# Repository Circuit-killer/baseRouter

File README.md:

BaseRouter
==========
Custom Router
- "socketable" is the current board.

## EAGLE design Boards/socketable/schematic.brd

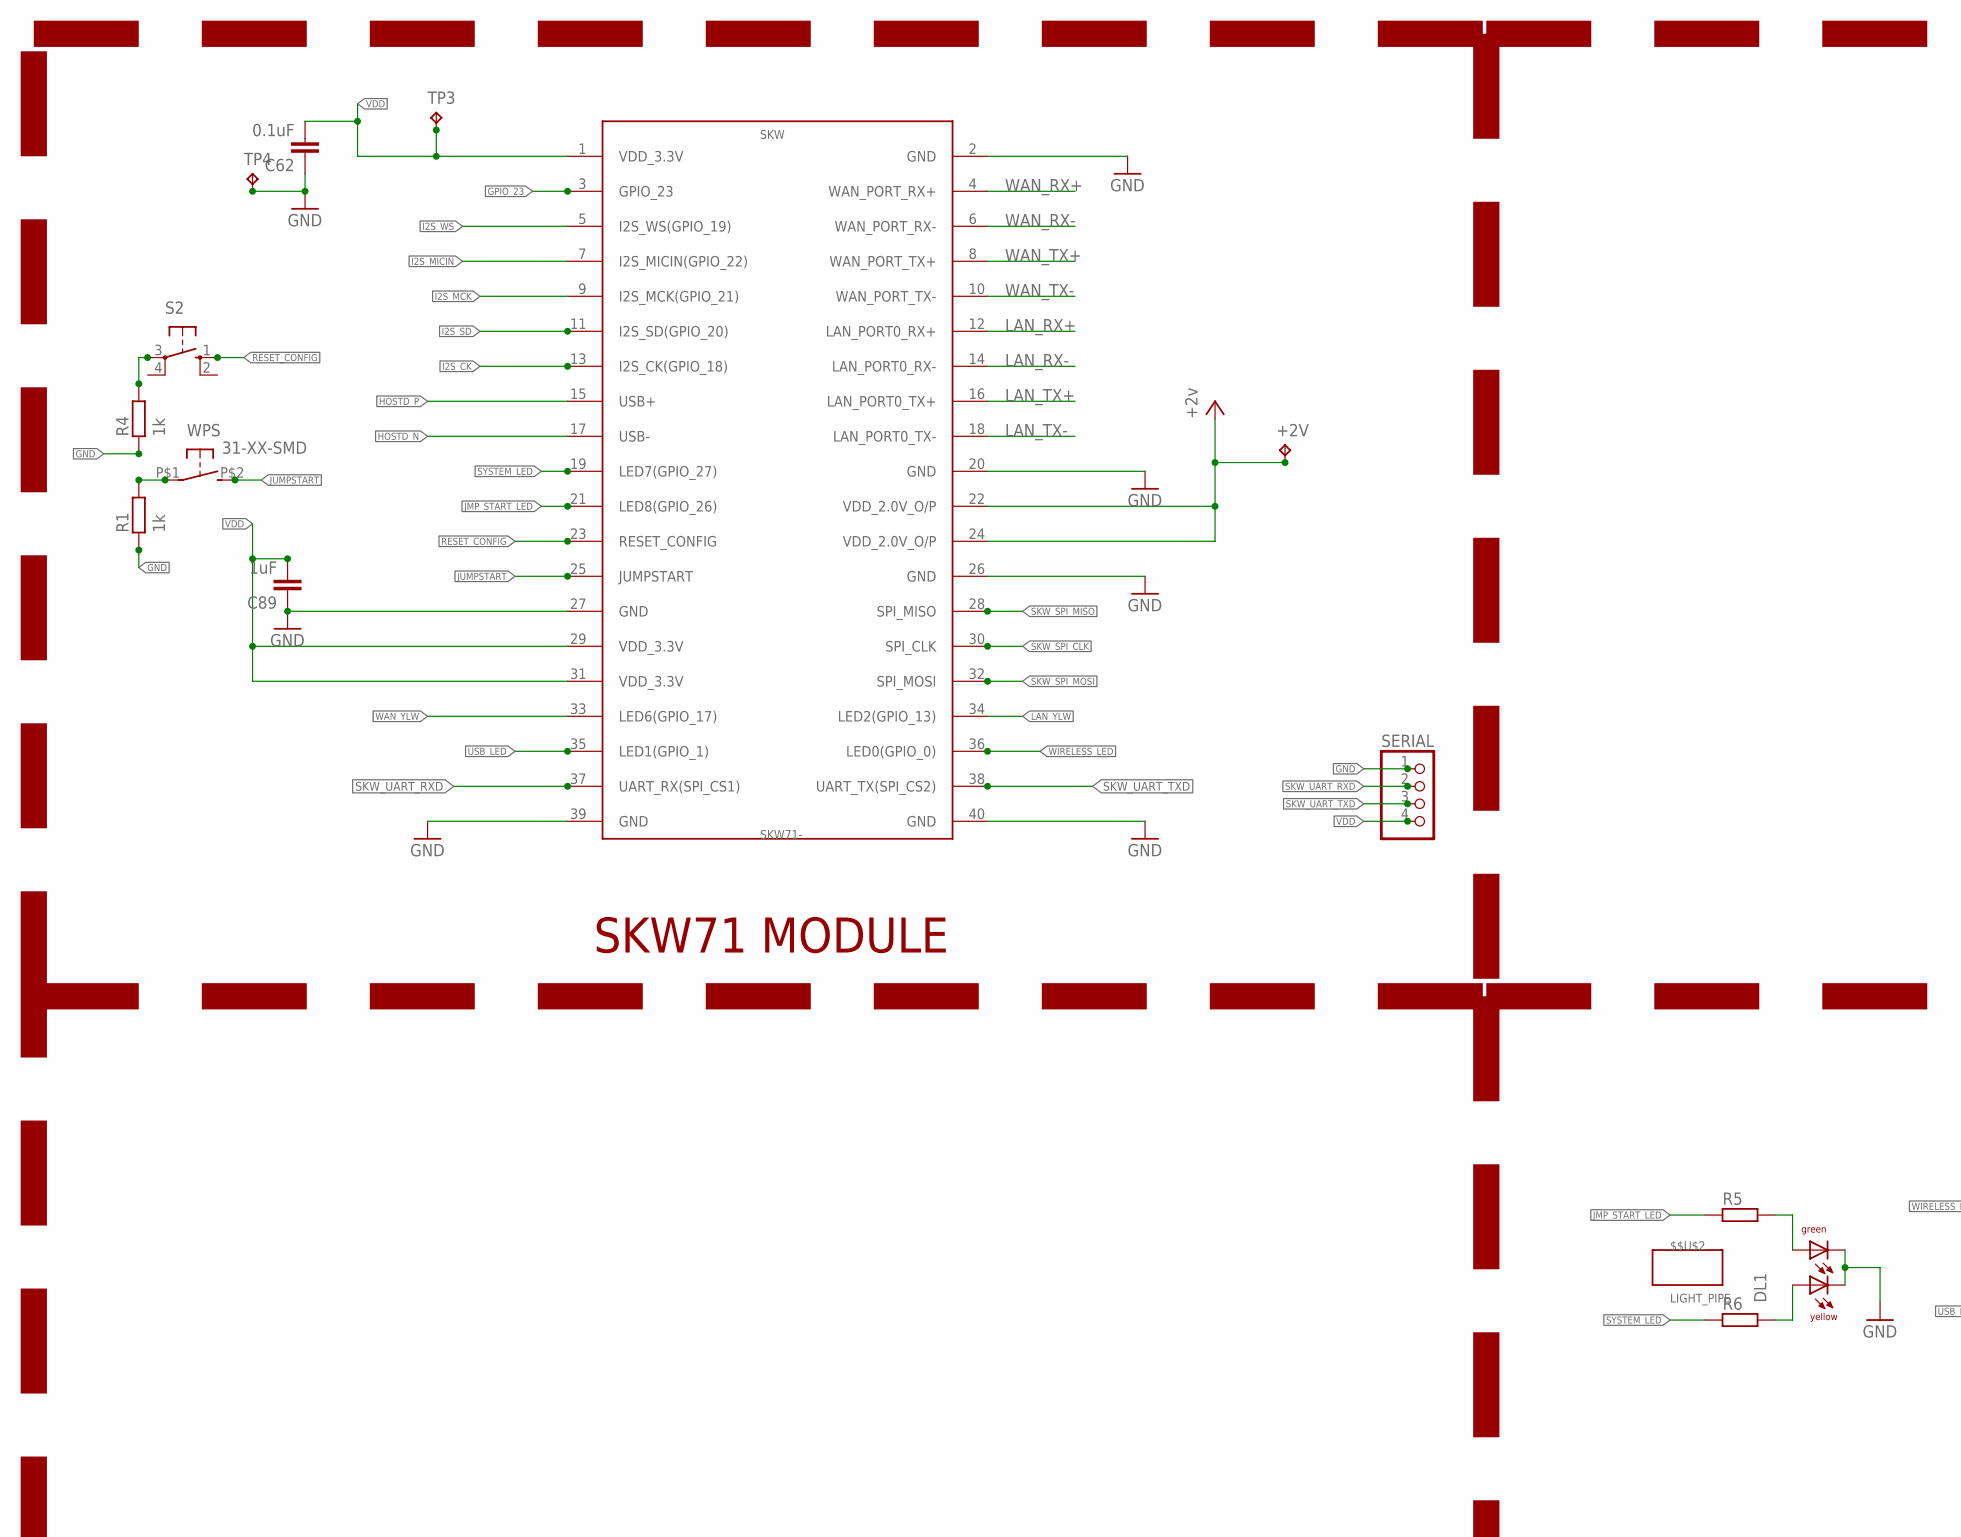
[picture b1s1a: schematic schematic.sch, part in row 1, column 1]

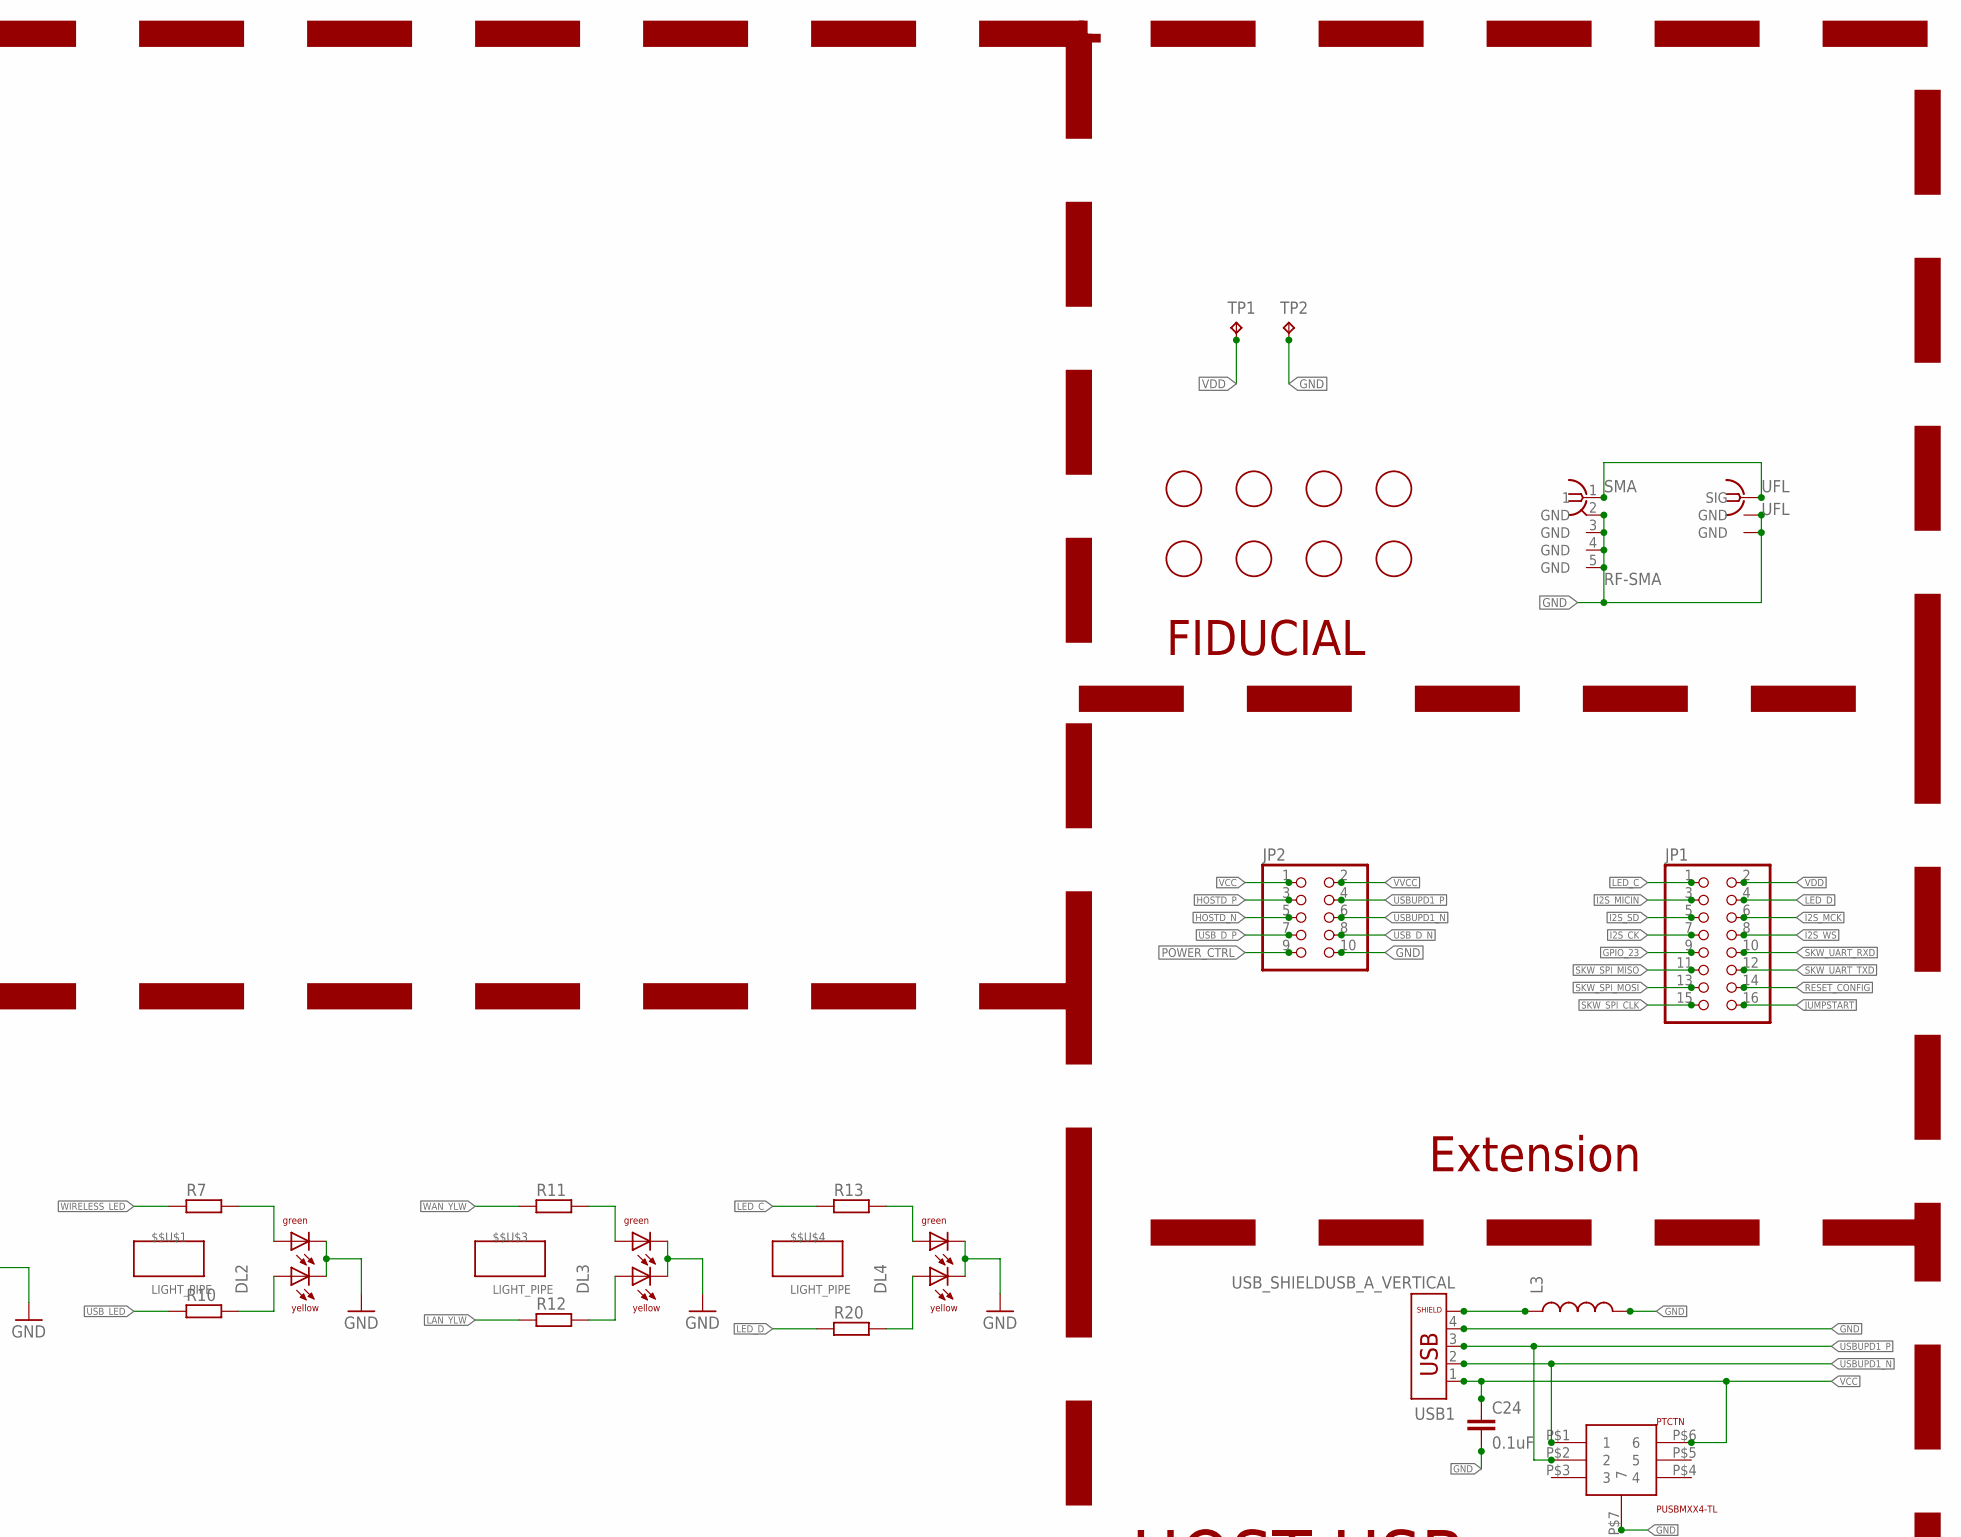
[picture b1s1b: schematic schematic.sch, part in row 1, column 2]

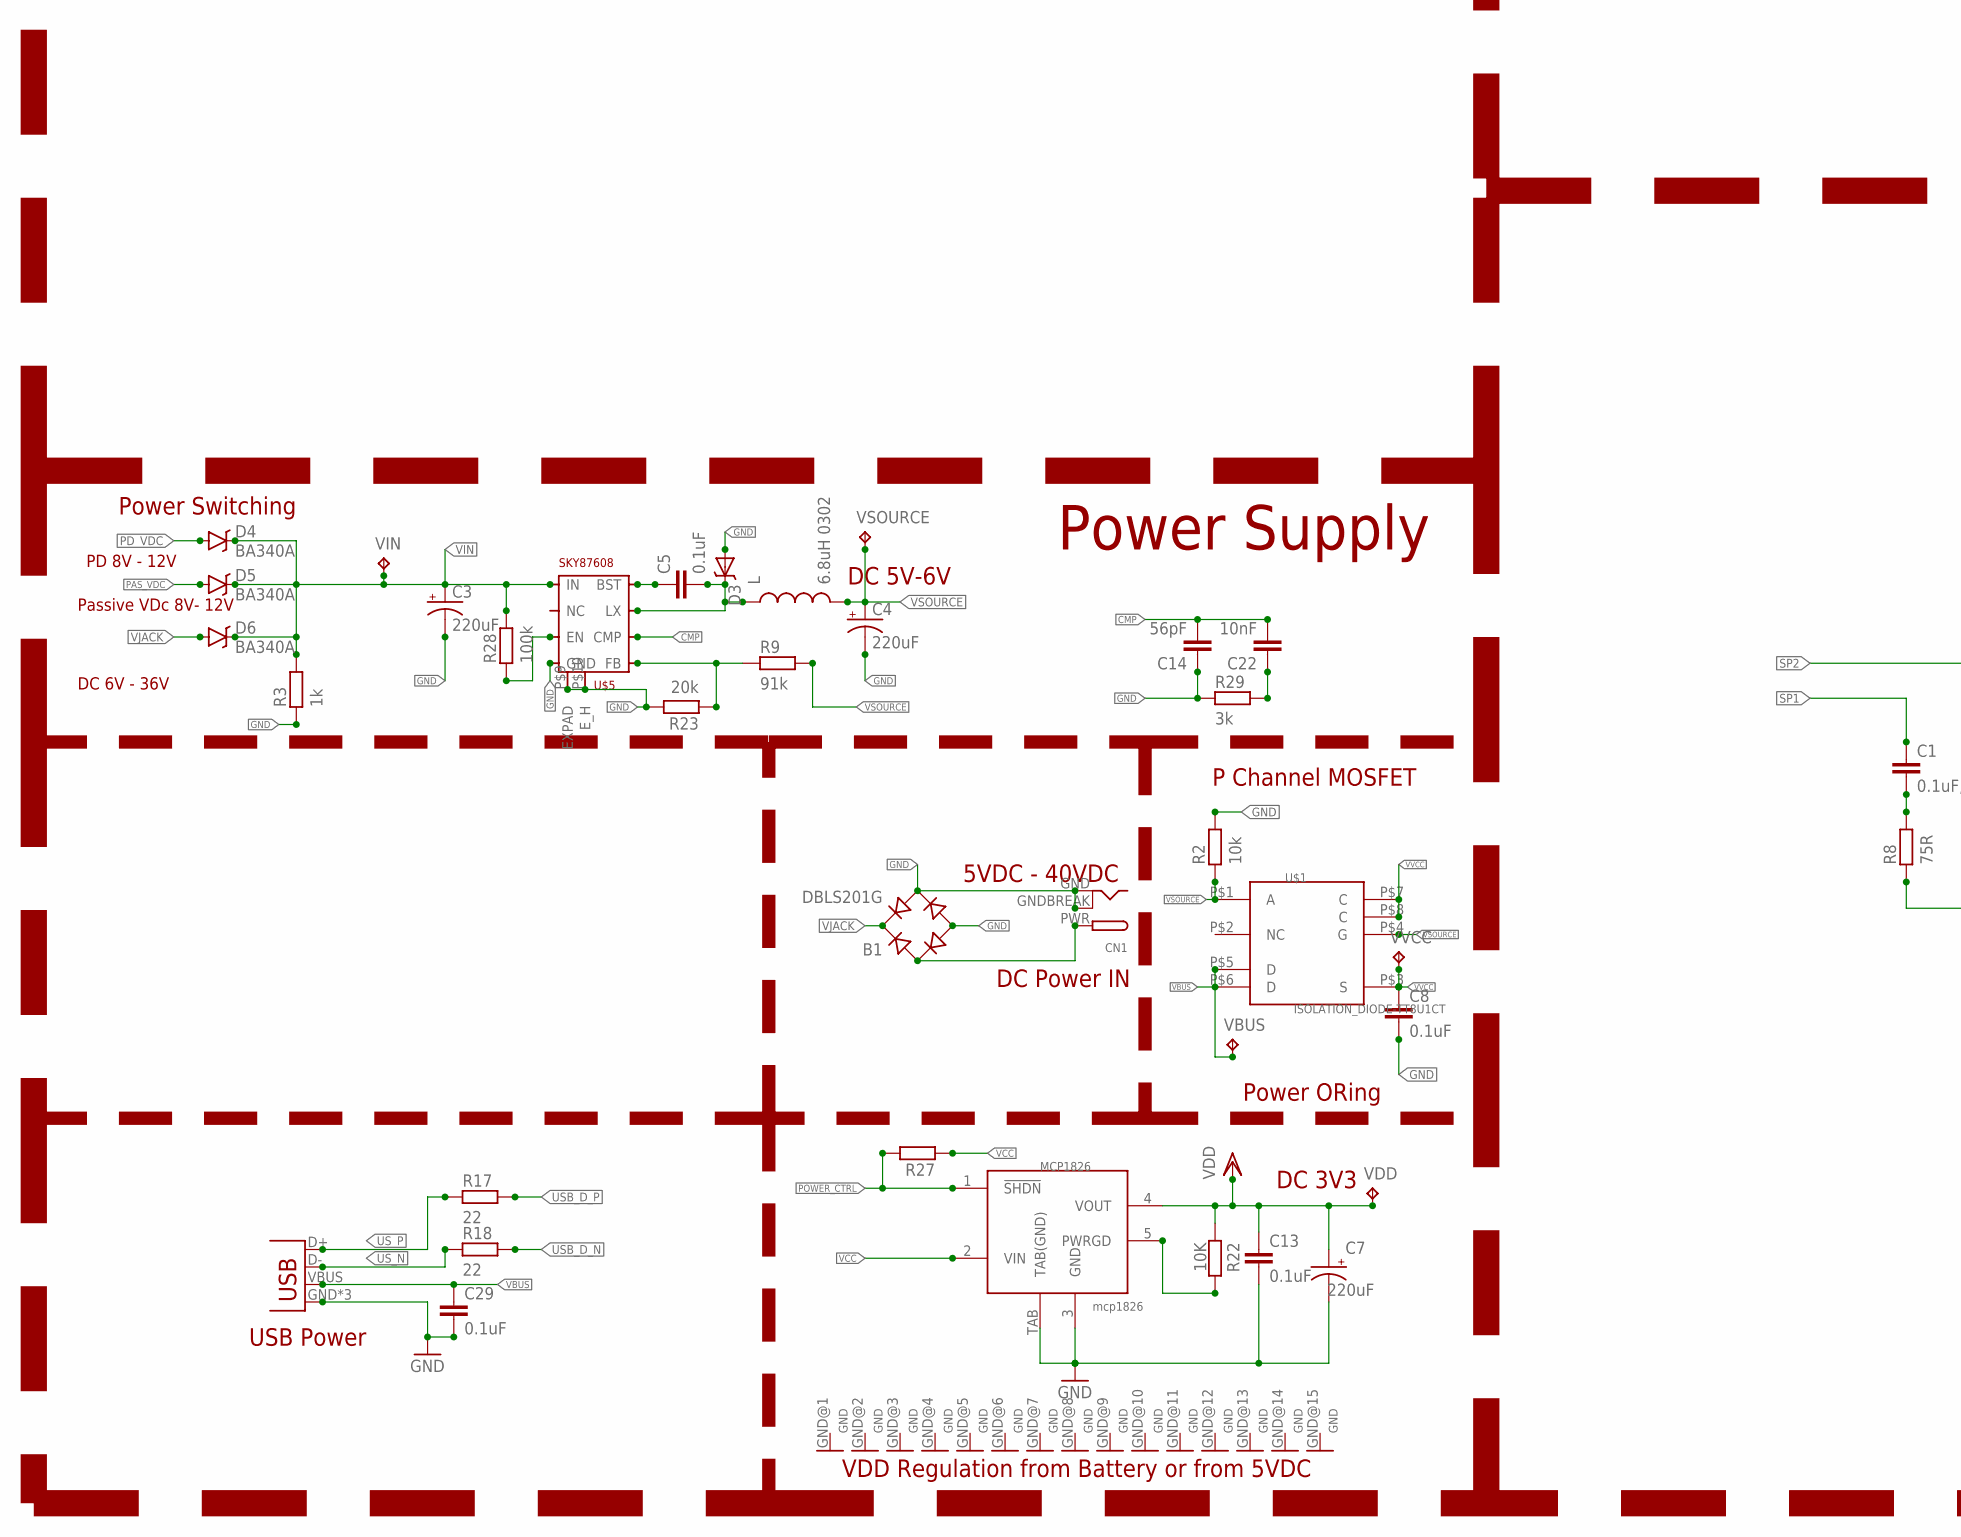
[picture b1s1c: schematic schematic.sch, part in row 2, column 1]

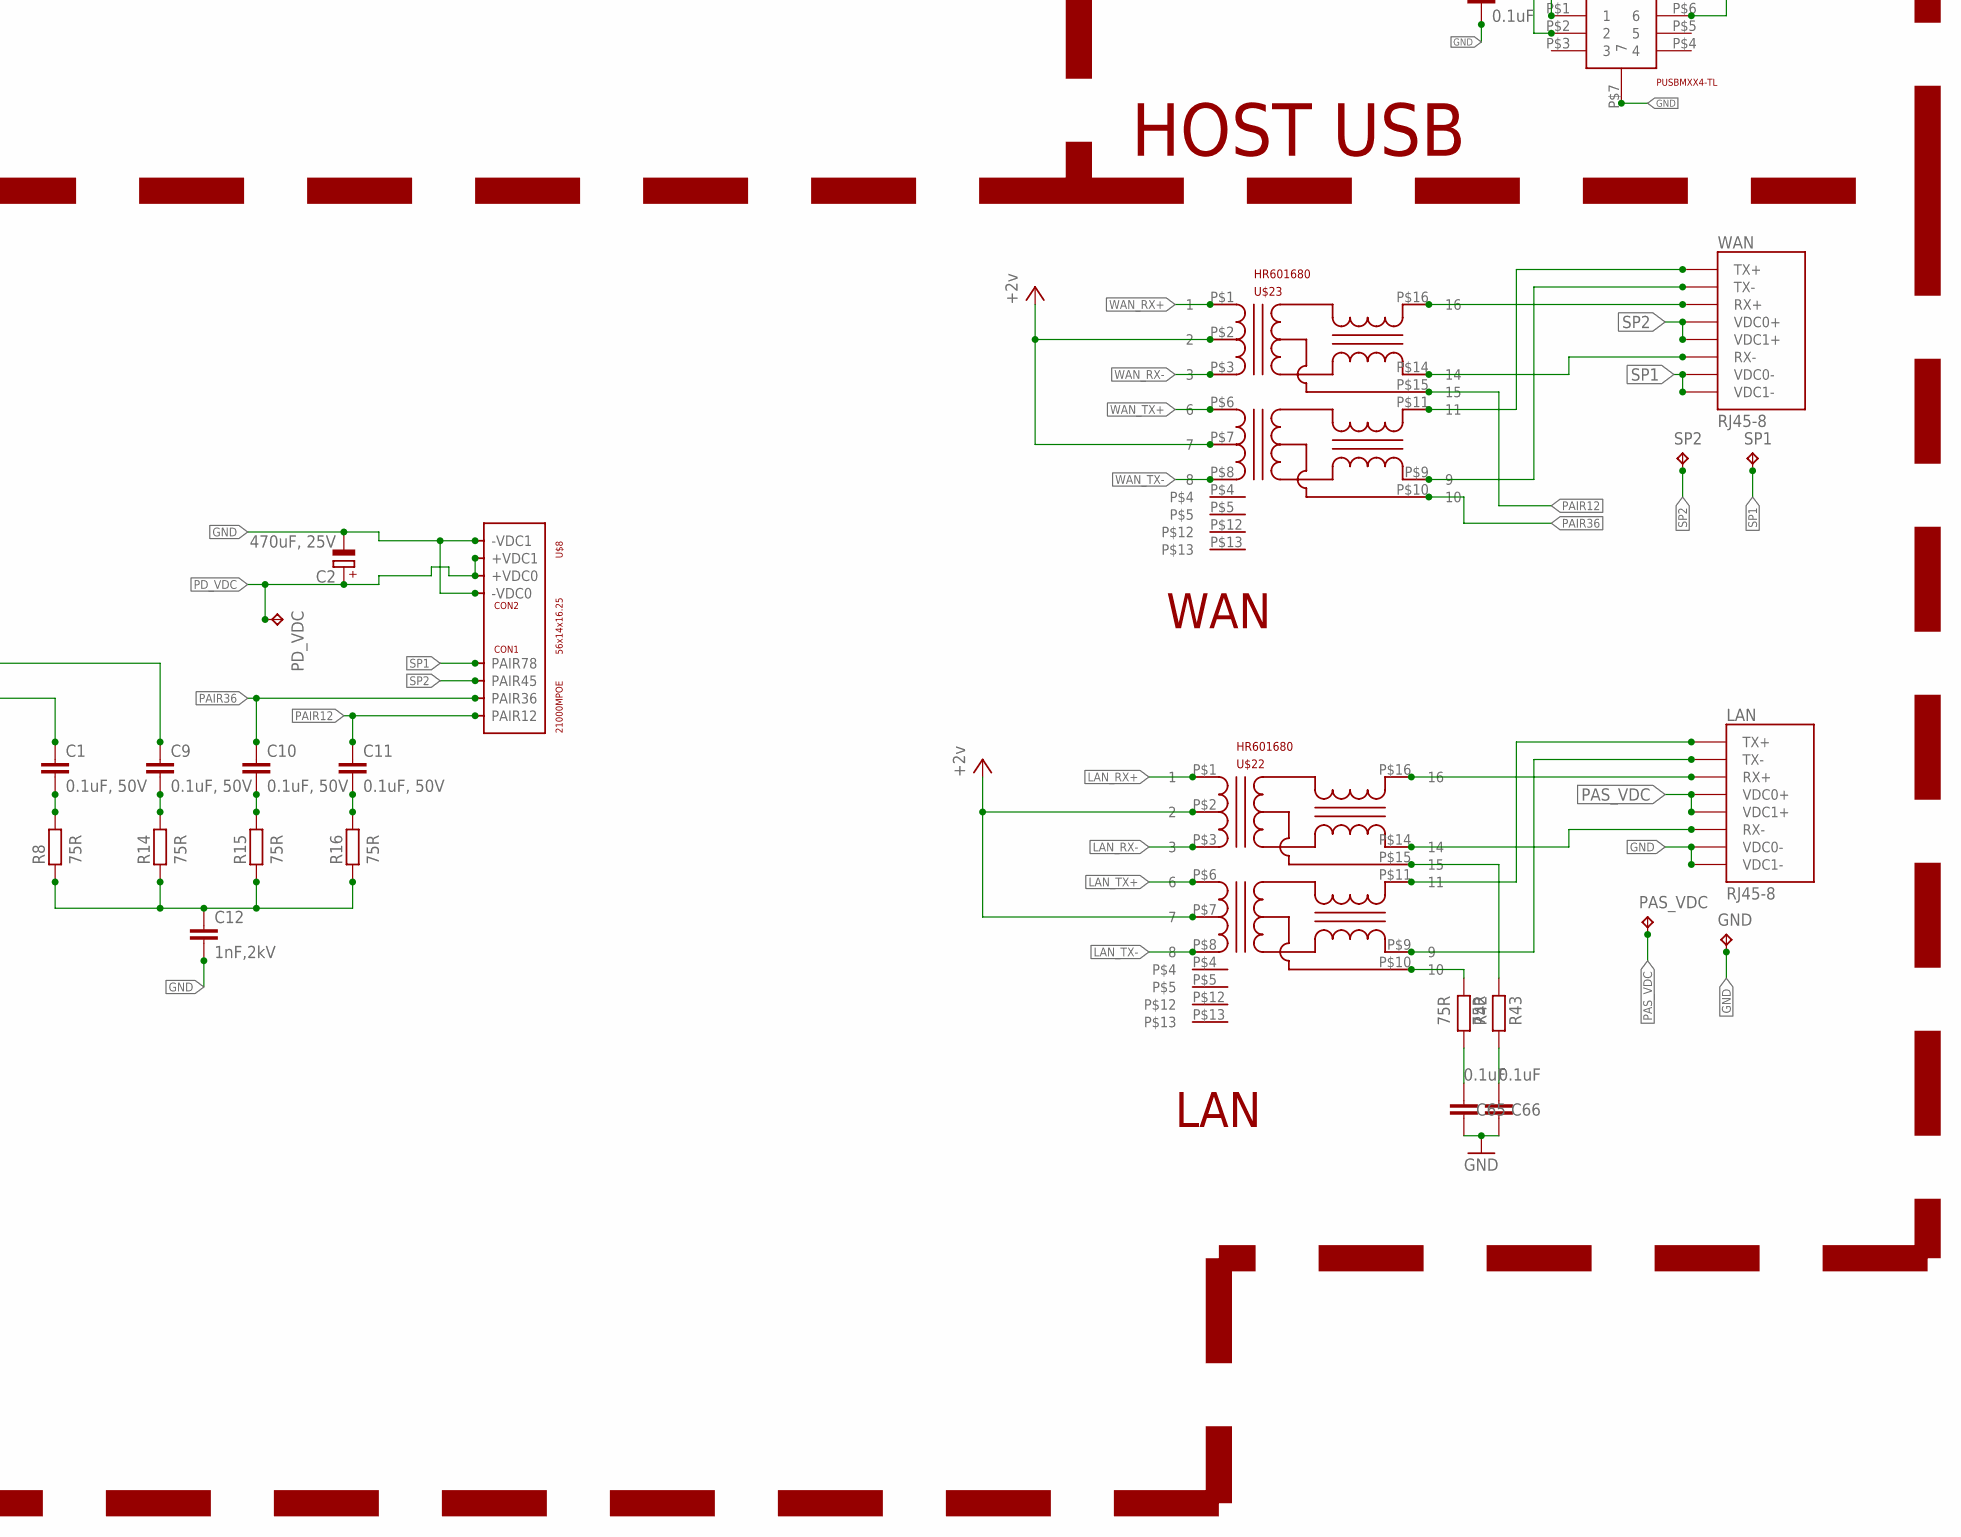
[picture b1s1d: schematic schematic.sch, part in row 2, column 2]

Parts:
$$U$1, $$U$2, $$U$3, $$U$4: LIGHT_PIPE; LIGHT-PIPE
+2V: TPB2,54; B2,54
B1: DBLS201G; DBS
C1, C9, C10, C11: 0.1uF, 50V; C0603
C2: 470uF, 25V; E3,5-10
C3: 220uF; E3,5-10
C4, C7: 220uF; E5-10,5
C5, C8, C13, C24, C29, C62, C65, C66: 0.1uF; C0603
C12: 1nF,2kV; C0603
C14: 56pF; C0603
C22: 10nF; C0603
C89: 1uF; C0603
CN1: DCBARRELPTH; DCJACK_2MM_PTH
D3: DIODE-SCHOTTKY_; SMA-DIODE
D4, D5, D6: BA340A; SMA-DIODE
DL1, DL2, DL3, DL4: DUOLED-1X2; DUOLED-C-0603
GND: TPB2,54; B2,54
JP1: PINHD-2X8; 2X08
JP2: PINHD-2X5; 2X05
JP4: USB-MICROB
L: 6.8uH 0302; SRN6045
L3: INDUCTOR0603; 0603
LAN: RJ45-8; RJHSE-5080-ND
MCP1826: mcp1826; SOT223-5
PAS_VDC: TPB2,54; B2,54
PD_VDC: TPB2,54; B2,54
PTCTN: PUSBMXX4-TL
R1, R3, R4: 1k; R0603
R2: 10k; R0603
R5, R6, R7, R10, R11, R12, R13, R20, R27: RESISTOR; R0603
R8, R14, R15, R16, R42, R43: 75R; R0603
R9: 91k; R0603
R17, R18: 22; R0603
R22: 10K; R0603
R23: 20k; R0603
R28: 100k; R0603
R29: 3k; R0603
S2: 10-XX; B3F-10XX
SERIAL: PINHD-1X4; 1X04
SKW: SKW71-; SKW71-SMT
SMA: RF-SMA; BU-SMA-H
SP1, SP2: TPB2,54; B2,54
TP1, TP2, TP3, TP4: TPB2,54; B2,54
U$1: ISOLATION_DIODE-TT8U1CT; 8-TSST
U$5: SKY87608; 8PIN-SOP-8L-EP
U$8: 21000MPOE
U$9, U$11, U$12, U$13, U$14, U$15, U$16, U$17: FIDUCIAL; FIDUCIAL_1MM
U$22, U$23: HR601680; SOIC-16
UFL: UFL
USB1: USB_SHIELDUSB_A_VERTICAL; USB_A_VERTICAL_PTH
VBUS: TPB2,54; B2,54
VDD: TPB2,54; B2,54
VIN: TPB2,54; B2,54
VSOURCE: TPB2,54; B2,54
VVCC: TPB2,54; B2,54
WAN: RJ45-8; RJHSE-5080-ND
WPS: 31-XX-SMD; BF3-31XX_SMD_PAD

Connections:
+2V: +2V.TP, SKW.22 (VDD_2.0V_O/P), SKW.24 (VDD_2.0V_O/P), U$22.P$2 (2), U$22.P$7 (7), U$23.P$2 (2), U$23.P$7 (7)
CMP: C14.2, C22.2, U$5.P$6 (CMP)
GND: B1.-, B1.AC2, C2.-, C3.-, C4.-, C7.-, C8.2, C12.2, C13.2, C14.1, C24.2, C29.2, C62.1, C65.1, C66.1, C89.1, CN1.GND, CN1.GNDBREAK, D3.A, DL1.C1, DL1.C2, DL2.C1, DL2.C2, DL3.C1, DL3.C2, DL4.C1, DL4.C2, GND.TP, JP2.10, JP4.GND, JP4.MT1 (GND), JP4.MT2 (GND), L3.2, LAN.P$7 (VDC0-), LAN.P$8 (VDC1-), MCP1826.3 (GND), MCP1826.GND@1 (GND), MCP1826.GND@2 (GND), MCP1826.GND@3 (GND), MCP1826.GND@4 (GND), MCP1826.GND@5 (GND), MCP1826.GND@6 (GND), MCP1826.GND@7 (GND), MCP1826.GND@8 (GND), MCP1826.GND@9 (GND), MCP1826.GND@10 (GND), MCP1826.GND@11 (GND), MCP1826.GND@12 (GND), MCP1826.GND@13 (GND), MCP1826.GND@14 (GND), MCP1826.GND@15 (GND), MCP1826.TAB (TAB(GND)), PTCTN.P$7 (7), R1.1, R2.2, R3.1, R4.1, R23.2, R29.1, SERIAL.1, SKW.2 (GND), SKW.20 (GND), SKW.26 (GND), SKW.27 (GND), SKW.39 (GND), SKW.40 (GND), SMA.2 (GND), SMA.3 (GND), SMA.4 (GND), SMA.5 (GND), TP2.TP, TP4.TP, U$5.P$4 (GND), U$5.P$9 (EXPAD), U$5.P$10 (E_H), U$8.P$5 (-VDC0), U$8.P$8 (-VDC1), UFL.GND@1 (GND), UFL.GND@2 (GND), USB1.4
GPIO_23: JP1.9, SKW.3 (GPIO_23)
HOSTD_N: JP2.5, SKW.17 (USB-)
HOSTD_P: JP2.3, SKW.15 (USB+)
I2S_CK: JP1.7, SKW.13 (I2S_CK(GPIO_18))
I2S_MCK: JP1.6, SKW.9 (I2S_MCK(GPIO_21))
I2S_MICIN: JP1.3, SKW.7 (I2S_MICIN(GPIO_22))
I2S_SD: JP1.5, SKW.11 (I2S_SD(GPIO_20))
I2S_WS: JP1.8, SKW.5 (I2S_WS(GPIO_19))
JMP_START_LED: R5.1, SKW.21 (LED8(GPIO_26))
JUMPSTART: JP1.16, SKW.25 (JUMPSTART), WPS.P$2 (S)
LAN_RX+: SKW.12 (LAN_PORT0_RX+), U$22.P$1 (1)
LAN_RX-: SKW.14 (LAN_PORT0_RX-), U$22.P$3 (3)
LAN_TX+: SKW.16 (LAN_PORT0_TX+), U$22.P$6 (6)
LAN_TX-: SKW.18 (LAN_PORT0_TX-), U$22.P$8 (8)
LAN_YLW: R12.1, SKW.34 (LED2(GPIO_13))
LED_C: JP1.1, R13.1
LED_D: JP1.4, R20.1
unnamed: DL2.A1, R7.2
unnamed: C5.2, D3.C, L.1, U$5.P$2 (LX)
unnamed: DL1.A1, R5.2
unnamed: DL2.A2, R10.2
unnamed: R1.2, WPS.P$1
unnamed: C1.2, R8.2
unnamed: R4.2, S2.3
unnamed: C9.2, R14.2
unnamed: SMA.1, UFL.SIG
unnamed: DL3.A2, R12.2
unnamed: C10.2, R15.2
unnamed: DL4.A1, R13.2
unnamed: MCP1826.5 (PWRGD), R22.2
unnamed: C12.1, R8.1, R14.1, R15.1, R16.1
unnamed: R28.1, U$5.P$7 (EN)
unnamed: C11.2, R16.2
unnamed: C5.1, U$5.P$8 (BST)
unnamed: R9.1, R23.1, U$5.P$5 (FB)
unnamed: DL4.A2, R20.2
unnamed: DL3.A1, R11.2
unnamed: C22.1, R29.2
unnamed: DL1.A2, R6.2
unnamed: L3.1, USB1.P$3 (5)
unnamed: B1.AC1, CN1.PWR
unnamed: U$23.P$16 (16), WAN.P$3 (RX+)
unnamed: U$23.P$14 (14), WAN.P$6 (RX-)
unnamed: U$23.P$11 (11), WAN.P$1 (TX+)
unnamed: U$23.P$9 (9), WAN.P$2 (TX-)
unnamed: R42.1, U$22.P$10 (10)
unnamed: LAN.P$2 (TX-), U$22.P$9 (9)
unnamed: LAN.P$1 (TX+), U$22.P$11 (11)
unnamed: R43.1, U$22.P$15 (15)
unnamed: LAN.P$6 (RX-), U$22.P$14 (14)
unnamed: LAN.P$3 (RX+), U$22.P$16 (16)
unnamed: C65.2, R42.2
unnamed: C66.2, R43.2
PAIR12: C11.1, U$8.P$1 (PAIR12), U$23.P$15 (15)
PAIR36: C10.1, U$8.P$2 (PAIR36), U$23.P$10 (10)
PAS_VDC: D5.A, LAN.P$4 (VDC0+), LAN.P$5 (VDC1+), PAS_VDC.TP
PD_VDC: C2.+, D4.A, PD_VDC.TP, U$8.P$6 (+VDC0), U$8.P$7 (+VDC1)
POWER_CTRL: JP2.9, MCP1826.1 (!SHDN), R27.2
RESET_CONFIG: JP1.14, S2.1 (S), SKW.23 (RESET_CONFIG)
SKW_SPI_CLK: JP1.15, SKW.30 (SPI_CLK)
SKW_SPI_MISO: JP1.11, SKW.28 (SPI_MISO)
SKW_SPI_MOSI: JP1.13, SKW.32 (SPI_MOSI)
SKW_UART_RXD: JP1.10, SERIAL.2, SKW.37 (UART_RX(SPI_CS1))
SKW_UART_TXD: JP1.12, SERIAL.3, SKW.38 (UART_TX(SPI_CS2))
SP1: C1.1, SP1.TP, U$8.P$4 (PAIR78), WAN.P$7 (VDC0-), WAN.P$8 (VDC1-)
SP2: C9.1, SP2.TP, U$8.P$3 (PAIR45), WAN.P$4 (VDC0+), WAN.P$5 (VDC1+)
SYSTEM_LED: R6.1, SKW.19 (LED7(GPIO_27))
USBUPD1_N: JP2.6, PTCTN.P$1 (1), USB1.2
USBUPD1_P: JP2.4, PTCTN.P$2 (2), USB1.3
USB_D_N: JP2.8, R18.2
USB_D_P: JP2.7, R17.2
USB_LED: R10.1, SKW.35 (LED1(GPIO_1))
US_N: JP4.D-, R18.1
US_P: JP4.D+, R17.1
VBUS: C29.1, JP4.VBUS, U$1.P$5 (D), U$1.P$6 (D), VBUS.TP
VCC: C24.1, JP2.1, MCP1826.2 (VIN), PTCTN.P$6 (6), R27.1, USB1.1
VDD: C7.+, C13.1, C62.2, C89.2, JP1.2, MCP1826.4 (VOUT), R22.1, SERIAL.4, SKW.1 (VDD_3.3V), SKW.29 (VDD_3.3V), SKW.31 (VDD_3.3V), TP1.TP, TP3.TP, VDD.TP
VIN: C3.+, D4.C, D5.C, D6.C, R3.2, R28.2, U$5.P$1 (IN), VIN.TP
VJACK: B1.+, D6.A
VSOURCE: C4.+, L.2, R2.1, R9.2, U$1.P$1 (A), U$1.P$4 (G), VSOURCE.TP
VVCC: C8.1, JP2.2, U$1.P$3 (S), U$1.P$7 (C), U$1.P$8 (C), VVCC.TP
WAN_RX+: SKW.4 (WAN_PORT_RX+), U$23.P$1 (1)
WAN_RX-: SKW.6 (WAN_PORT_RX-), U$23.P$3 (3)
WAN_TX+: SKW.8 (WAN_PORT_TX+), U$23.P$6 (6)
WAN_TX-: SKW.10 (WAN_PORT_TX-), U$23.P$8 (8)
WAN_YLW: R11.1, SKW.33 (LED6(GPIO_17))
WIRELESS_LED: R7.1, SKW.36 (LED0(GPIO_0))

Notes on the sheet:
SKW71 MODULE
5VDC - 40VDC
PD 8V - 12V
Passive VDc 8V- 12V
Power Switching
USB Power
VDD Regulation from Battery or from 5VDC
DC Power IN
Power Supply
DC 5V-6V
DC 6V - 36V
DC 3V3
Power ORing
P Channel MOSFET
HOST USB
Extension
FIDUCIAL
LAN
WAN

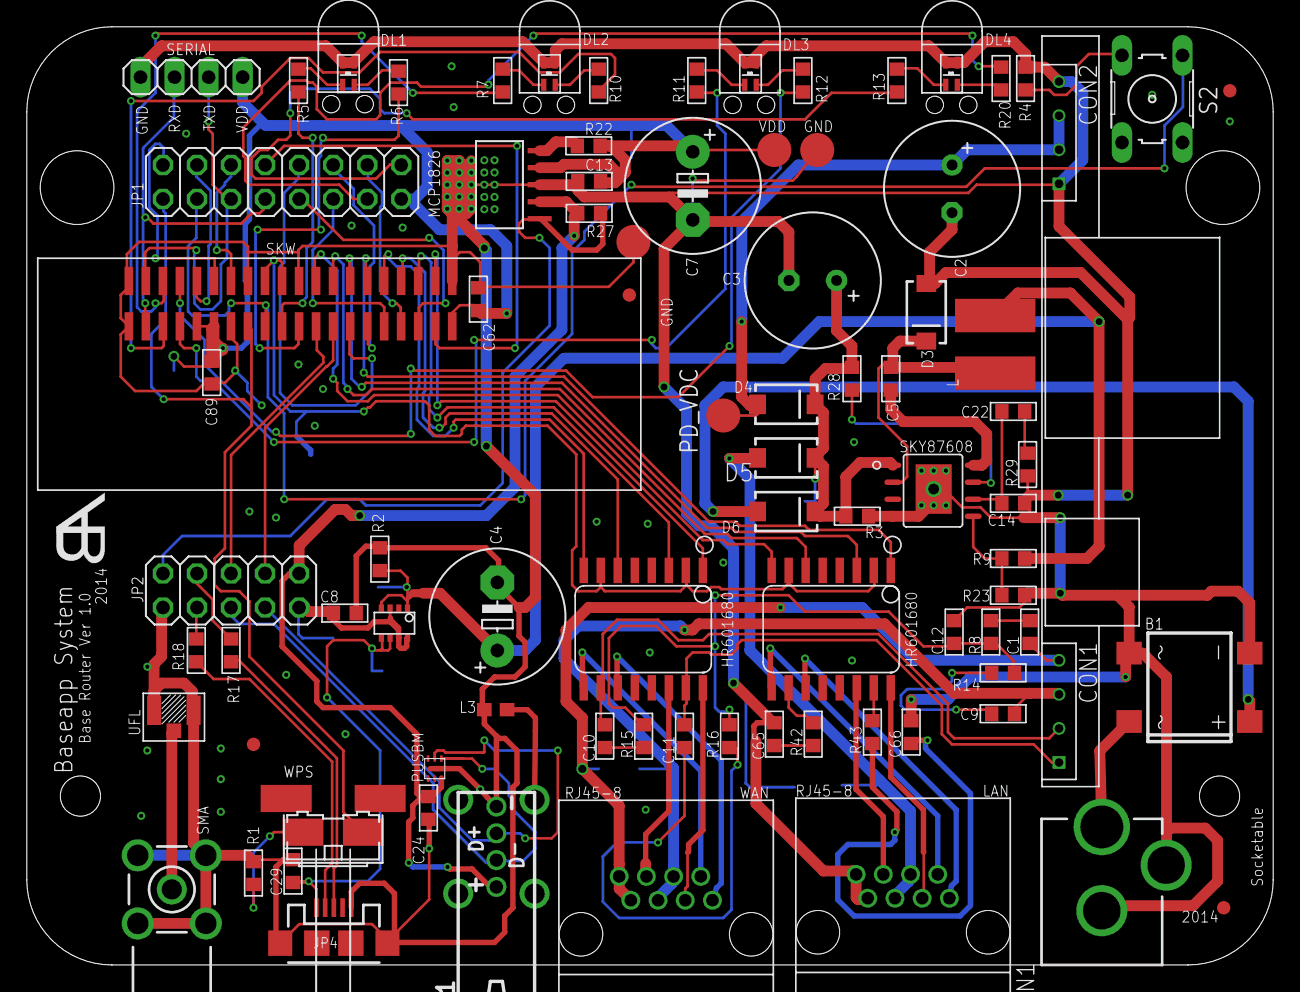
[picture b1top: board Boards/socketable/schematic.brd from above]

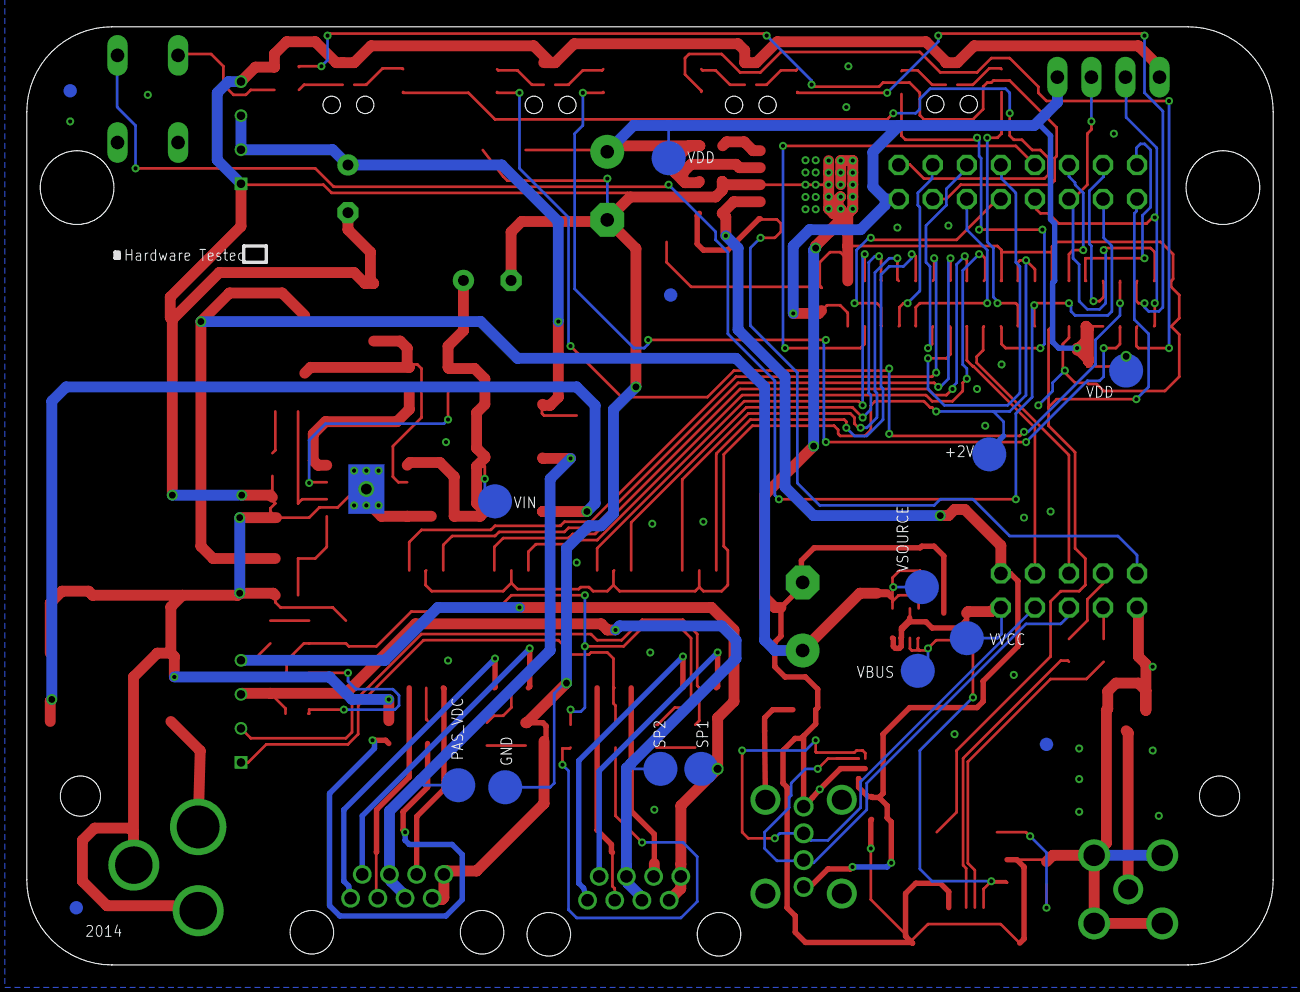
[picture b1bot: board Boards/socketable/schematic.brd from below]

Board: 2 copper layers, 93.0 x 70.0 mm, 104 parts (15 on the bottom side), 90 nets.

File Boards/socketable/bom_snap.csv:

Qty,Part Number,Device,Package,Ref. Desig.,Description,,Digikey Part
1,,10-XX,B3F-10XX,S2,OMRON SWITCH
1,,DCBARRELPTH,DCJACK_2MM_PTH,CN1,2.0mm DC Barrel Jack
4,,DUOLED-1X2,DUOLED-C-0603,"DL1, DL2, DL3, DL4",Digikey No :- __754-1146-1-ND__
1,,INDUCTOR0603,603,L3,Inductors
1,,PINHD-1X4,1X04,SERIAL,PIN HEADER
1,,PINHD-2X5,2X05,JP2,PIN HEADER
1,,PINHD-2X8,2X08,JP1,PIN HEADER
9,,RESISTOR,R0603,"R5, R6, R7, R10, R11, R12, R13, R20, R27",Resistance
8,0.1uF,CAPACITOR,C0603,"C5, C8, C13, C24, C29, C62, C65, C66","C0402 & C0603 are general chip capacitorsFilm Capacitor, 400V's Mouser Part No :- __ECQ-E4474KF__"
4,"0.1uF, 50V",CAPACITOR,C0603,"C1, C9, C10, C11","C0402 & C0603 are general chip capacitorsFilm Capacitor, 400V's Mouser Part No :- __ECQ-E4474KF__"
1,100k,RESISTOR,R0603,R28,Resistance
1,10K,RESISTOR,R0603,R22,Resistance,,Link
1,10k,RESISTOR,R0603,R2,Resistance
1,10nF,CAPACITOR,C0603,C22,"C0402 & C0603 are general chip capacitorsFilm Capacitor, 400V's Mouser Part No :- __ECQ-E4474KF__"
3,1k,RESISTOR,R0603,"R1, R3, R4",Resistance
1,"1nF,2kV",CAPACITOR,C0603,C12,"C0402 & C0603 are general chip capacitorsFilm Capacitor, 400V's Mouser Part No :- __ECQ-E4474KF__"
1,1uF,CAPACITOR,C0603,C89,"C0402 & C0603 are general chip capacitorsFilm Capacitor, 400V's Mouser Part No :- __ECQ-E4474KF__"
1,20k,RESISTOR,R0603,R23,Resistance
1,21000MPOE,21000MPOE,21000MPOE,U$8,,,NA
2,22,RESISTOR,R0603,"R17, R18",Resistance
1,220uF,CPOL-USE3.5-10,"E3,5-10",C3,"POLARIZED CAPACITOR, American symbol"
2,220uF,CPOL-USE5-10.5,"E5-10,5","C4, C7","POLARIZED CAPACITOR, American symbol"
1,31-XX-SMD,31-XX-SMD,BF3-31XX_SMD_PAD,WPS
1,3k,RESISTOR,R0603,R29,Resistance
1,"470uF, 25V",CPOL-EUE3.5-10,"E3,5-10",C2,"POLARIZED CAPACITOR, European symbol"
1,56pF,CAPACITOR,C0603,C14,"C0402 & C0603 are general chip capacitorsFilm Capacitor, 400V's Mouser Part No :- __ECQ-E4474KF__"
1,6.8uH 0302,INDUCTORBOURNS_SRN6045,SRN6045,L,Inductors
6,75R,RESISTOR,R0603,"R8, R14, R15, R16, R42, R43",Resistance
1,91k,RESISTOR,R0603,R9,Resistance
3,BA340A,B340A,SMA-DIODE,"D4, D5, D6",Schottky Diode,,B340A-FDICT-ND
1,DBLS201G,DBLS201G,DBS,B1,Single Phase 1.0 AMP Glass Passivated Bridge Rectifier,,DF04SCT-ND
1,DIODE-SCHOTTKY_,DIODE-SCHOTTKY_,SMA-DIODE,D3
8,FIDUCIAL,FIDUCIAL,FIDUCIAL_1MM,"U$9, U$11, U$12, U$13, U$14, U$15, U$16, U$17","For use by pick and place machines to calibrate the vision/machine, 1mm"
2,HR601680,HR601680,SOIC-16,"U$22, U$23",,,NA
1,ISOLATION_DIODE-TT8U1CT,ISOLATION_DIODE-TT8U1CT,8-TSST,U$1,Digikey No :- __FDFMA2P857CT-ND__ (6-WDFN).,,__FDFMA2P857CT-ND__
4,LIGHT_PIPE,LIGHT_PIPE,LIGHT-PIPE,"$$U$1, $$U$2, $$U$3, $$U$4",Digikey No :- __492-1313-ND__,, __492-1313-ND__
1,PUSBMXX4-TL,PUSBMXX4-TL,PUSBMXX4-TL,PTCTN,,,568-10921-1-ND
1,RF-SMA,RF-SMA,BU-SMA-H,SMA
2,RJ45-8,RJ45-8,RJHSE-5080-ND,"LAN, WAN",RJ45 Jack,,RJHSE-5080-ND
1,SKW71-,SKW71-,SKW71-SMT,SKW,,,NA
1,SKY87608,SKY87608,8PIN-SOP-8L-EP,U$5,,,NA
15,"TPB2,54","TPB2,54","B2,54","+2V, GND, PAS_VDC, PD_VDC, SP1, SP2, TP1, TP2, TP3, TP4, VBUS, VDD, VIN, VSOURCE, VVCC",Test pad
1,UFL,UFL,UFL,UFL,DIGIKEY NUMBER :- H9161-ND,,H9161-ND
1,USB-MICROB,USB-MICROB,USB-MICROB,JP4,USB Connectors,,609-4616-1-ND
1,USB_SHIELDUSB_A_VERTICAL,USB_SHIELDUSB_A_VERTICAL,USB_A_VERTICAL_PTH,USB1,,,609-1041-ND
1,mcp1826,MCP1825T,SOT223-5,MCP1826,Digikey No:- __MCP1825T-5002E/DCCT-ND__,,MCP1825T-5002E/DCCT-ND

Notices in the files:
parts and their libraries:
SparkFun-Aesthetics: Licensing: CC v3.0 Share-Alike You are welcome to use this library for commercial purposes.
SparkFun-Capacitors: Licensing: Creative Commons ShareAlike 4.0 International - https://creativecommons.org/licenses/by-sa/4.0
